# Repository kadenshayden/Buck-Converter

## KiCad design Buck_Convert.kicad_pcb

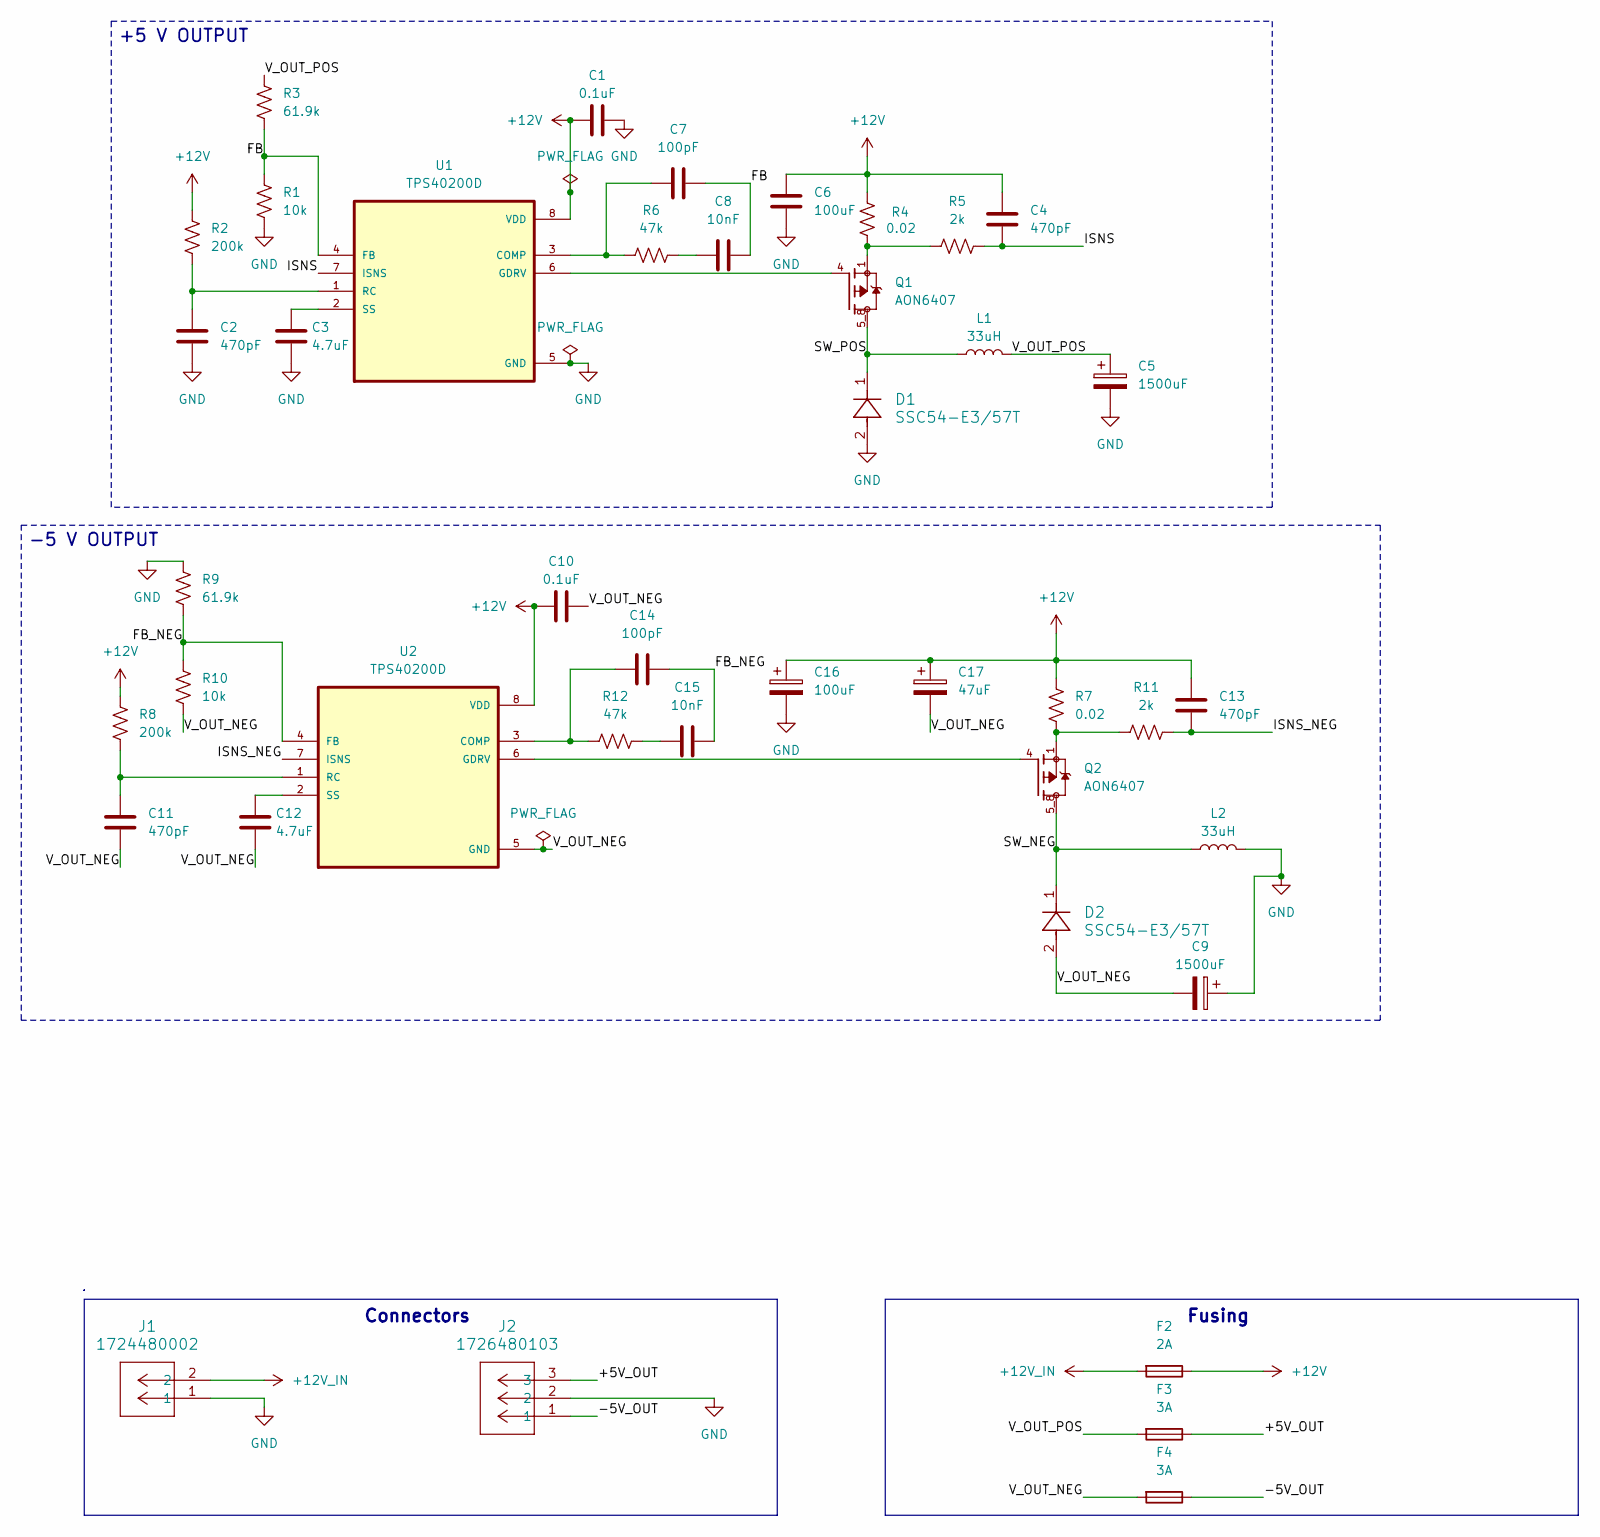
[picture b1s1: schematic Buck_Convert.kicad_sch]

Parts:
C1, C10: 0.1uF; C_0805_2012Metric
C2, C4, C11, C13: 470pF; C_0805_2012Metric
C3, C12: 4.7uF; C_1206_3216Metric
C5, C9: 1500uF; CP_Elec_16x17.5; MPN AFK158M35P44T-F
C6, C16: 100uF; CP_Elec_6.3x7.7
C7, C14: 100pF; C_0805_2012Metric
C8, C15: 10nF; C_0805_2012Metric
C17: 47uF; CP_Elec_6.3x5.8
D1, D2: SSC54-E3/57T; DIODE_DO214AB
F2: 2A; Fuse_1206_3216Metric
F3, F4: 3A; Fuse_1206_3216Metric
J1: 1724480002; CONN_SD-172448-0000_02_MOL
J2: 1726480103; CONN_SD-172648-0000_03_MOL
L1, L2: 33uH; SRP1038AA-330M; MPN SRP1038AA-330M
Q1, Q2: AON6407; TRANS_AON6407; MPN AON6407
R1, R10: 10k; R_0805_2012Metric
R2, R8: 200k; R_0805_2012Metric
R3, R9: 61.9k; R_0805_2012Metric
R4, R7: 0.02; R_2512_6332Metric
R5, R11: 2k; R_0805_2012Metric
R6, R12: 47k; R_0805_2012Metric
U1, U2: TPS40200D; SOIC127P599X175-8N; MPN TPS40200D

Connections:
+12V: C1.1, C4.1, C6.1, C10.1, C13.1, C16.1, C17.1, F2.1, R2.1, R4.1, R7.1, R8.1, U1.8 (VDD), U2.8 (VDD)
+12V_IN: F2.2, J1.2
/+5V_OUT: F3.1, J2.3
/-5V_OUT: F4.1, J2.1
/FB: C7.2, C8.2, R1.1, R3.2, U1.4 (FB)
/FB_NEG: C14.2, C15.2, R9.2, R10.1, U2.4 (FB)
/ISNS: C4.2, R5.2, U1.7 (ISNS)
/ISNS_NEG: C13.2, R11.2, U2.7 (ISNS)
/SW_NEG: D2.1, L2.1, Q2.5_8
/SW_POS: D1.1, L1.1, Q1.5_8
/V_OUT_NEG: C9.2, C10.2, C11.2, C12.2, C17.2, D2.2, F4.2, R10.2, U2.5 (GND)
/V_OUT_POS: C5.1, F3.2, L1.2, R3.1
GND: C1.2, C2.2, C3.2, C5.2, C6.2, C9.1, C16.2, D1.2, J1.1, J2.2, L2.2, R1.2, R9.1, U1.5 (GND)
unnamed: C8.1, R6.2
unnamed: C15.1, R12.2
unnamed: Q1.1, Q1.2, Q1.3, R4.2, R5.1
unnamed: Q2.1, Q2.2, Q2.3, R7.2, R11.1
unnamed: C7.1, R6.1, U1.3 (COMP)
unnamed: Q1.4, U1.6 (GDRV)
unnamed: C2.1, R2.2, U1.1 (RC)
unnamed: C3.1, U1.2 (SS)
unnamed: C14.1, R12.1, U2.3 (COMP)
unnamed: Q2.4, U2.6 (GDRV)
unnamed: C11.1, R8.2, U2.1 (RC)
unnamed: C12.1, U2.2 (SS)

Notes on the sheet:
Connectors
Fusing
-5 V OUTPUT
+5 V OUTPUT

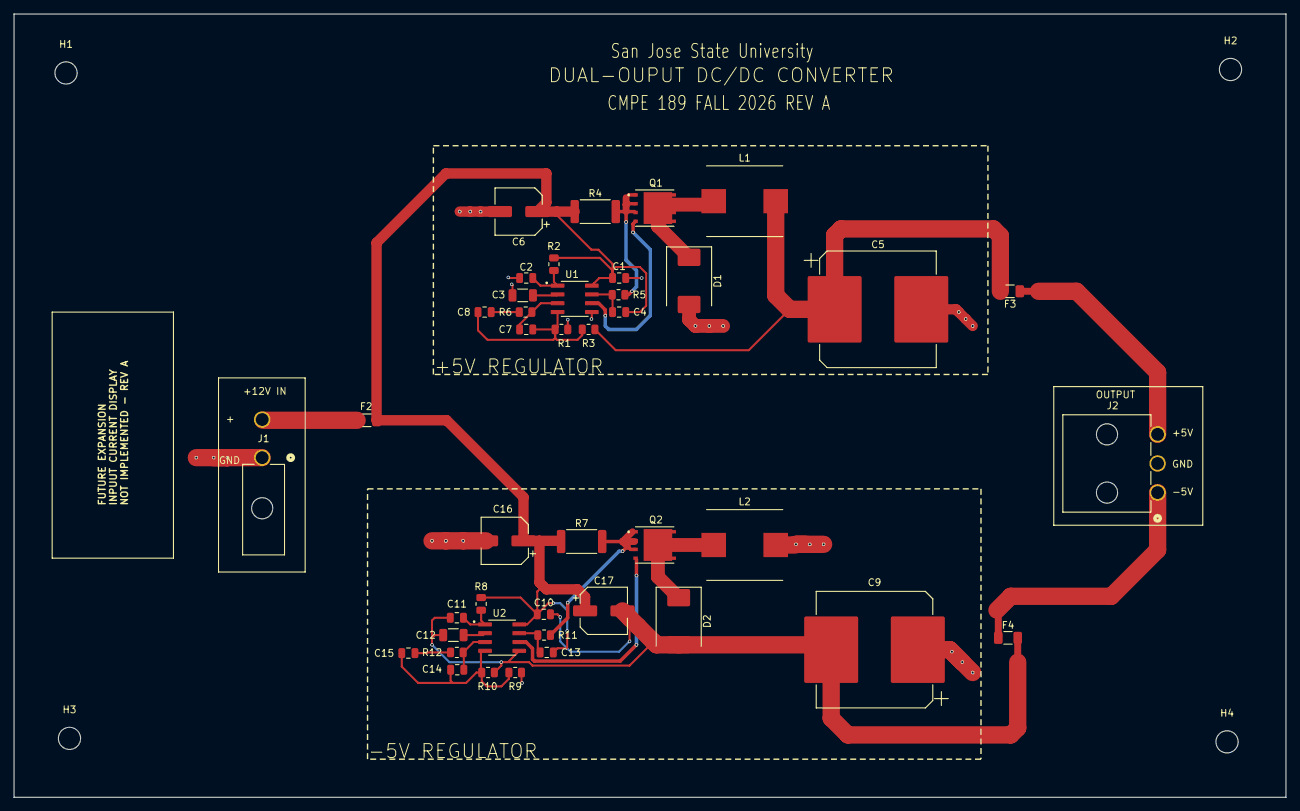
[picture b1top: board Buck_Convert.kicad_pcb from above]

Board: 4 copper layers, 183.5 x 113.0 mm, 46 parts (0 on the bottom side), 25 nets.

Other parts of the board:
H1, H2, H3, H4: MountingHole_3.2mm_M3

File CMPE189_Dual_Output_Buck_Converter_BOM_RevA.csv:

"Reference","Qty","Value","DNP","Exclude from BOM","Exclude from Board","Footprint","Datasheet","MANUFACTURER","MPN","Description"
"C1,C10","2","0.1uF","","","","Capacitor_SMD:C_0805_2012Metric","","","","Unpolarized capacitor"
"C2,C4,C11,C13","4","470pF","","","","Capacitor_SMD:C_0805_2012Metric","","","","Unpolarized capacitor"
"C3,C12","2","4.7uF","","","","Capacitor_SMD:C_1206_3216Metric","","","","Unpolarized capacitor"
"C5,C9","2","1500uF","","","","Capacitor_SMD:CP_Elec_16x17.5","kicad-embed://AFK158M35P44T-F_Cap.pdf","","AFK158M35P44T-F","Polarized capacitor"
"C6,C16","2","100uF","","","","Capacitor_SMD:CP_Elec_6.3x7.7","","","","Polarized capacitor,Unpolarized capacitor"
"C7,C14","2","100pF","","","","Capacitor_SMD:C_0805_2012Metric","","","","Unpolarized capacitor"
"C8,C15","2","10nF","","","","Capacitor_SMD:C_0805_2012Metric","","","","Unpolarized capacitor"
"C17","1","47uF","","","","Capacitor_SMD:CP_Elec_6.3x5.8","","","","Polarized capacitor"
"D1,D2","2","SSC54-E3/57T","","","","Diode_SMD:D_SMC","https://www.vishay.com/doc?88885","","",""
"F2","1","2A","","","","Fuse:Fuse_1206_3216Metric","","","","Fuse"
"F3,F4","2","3A","","","","Fuse:Fuse_1206_3216Metric","","","","Fuse"
"J1","1","1724480002","","","","Molex_2P:CONN_SD-172448-0000_02_MOL","https://www.molex.com/en-us/products/part-detail-pdf/1724480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","","",""
"J2","1","1726480103","","","","Molex_3P:CONN_SD-172648-0000_03_MOL","https://www.molex.com/en-us/products/part-detail-pdf/1726480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","","",""
"L1,L2","2","33uH","","","","L1_Footprint:SRP1038AA-330M","","","SRP1038AA-330M","Inductor"
"Q1,Q2","2","AON6407","","","","AON6407:TRANS_AON6407","https://s3.amazonaws.com/snapeda/datasheet/AON6407_Alpha_&.pdf","Alpha &","AON6407","P-Channel 30 V 32A (Ta), 85A (Tc) 7.3W (Ta), 83W (Tc) Surface Mount 8-DFN (5x6)"
"R1,R10","2","10k","","","","Resistor_SMD:R_0805_2012Metric","","","","Resistor, US symbol"
"R2,R8","2","200k","","","","Resistor_SMD:R_0805_2012Metric","","","","Resistor, US symbol"
"R3,R9","2","61.9k","","","","Resistor_SMD:R_0805_2012Metric","","","","Resistor, US symbol"
"R4,R7","2","0.02","","","","Resistor_SMD:R_2512_6332Metric","","","","Resistor, US symbol"
"R5,R11","2","2k","","","","Resistor_SMD:R_0805_2012Metric","","","","Resistor, US symbol"
"R6,R12","2","47k","","","","Resistor_SMD:R_0805_2012Metric","","","","Resistor, US symbol"
"U1,U2","2","TPS40200D","","","","TPS40200D:SOIC127P599X175-8N","http://www.ti.com/lit/gpn/tps40200","Texas Instruments","TPS40200D","Wide Input Non-Synchronous Buck DC/DC Controller"
